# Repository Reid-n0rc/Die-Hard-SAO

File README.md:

# Die Hard SAO
 Come out to the coast, have a few laughs...

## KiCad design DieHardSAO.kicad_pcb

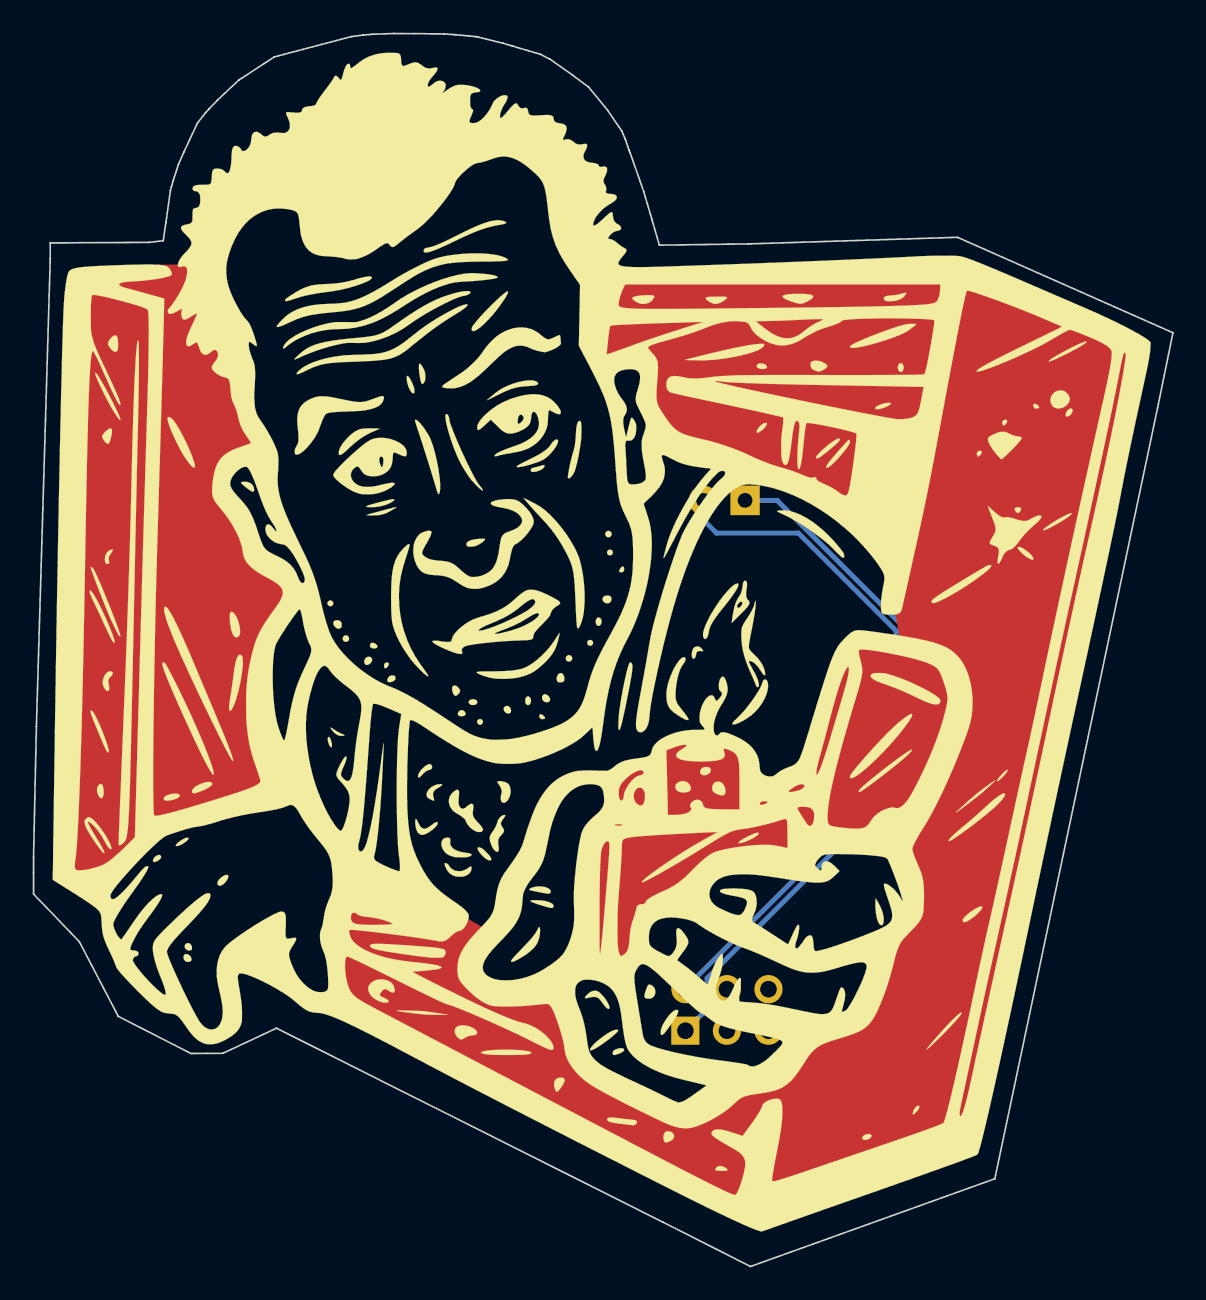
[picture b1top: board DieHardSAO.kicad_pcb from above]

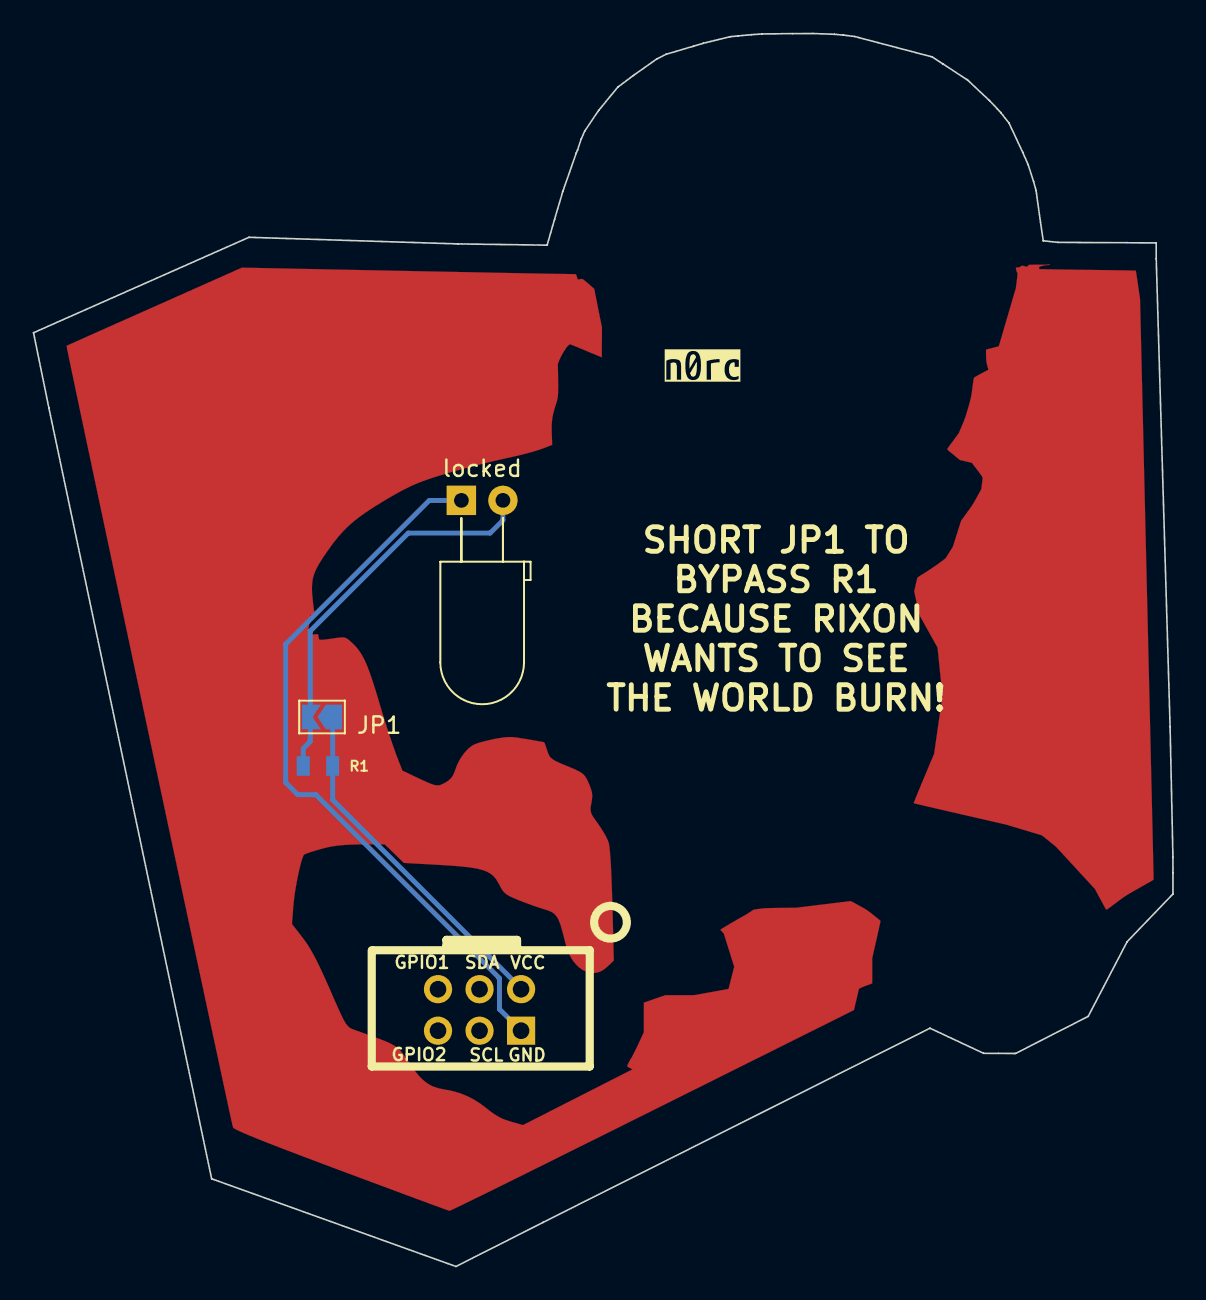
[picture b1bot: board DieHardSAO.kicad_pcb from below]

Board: 2 copper layers, 69.7 x 75.4 mm, 5 parts (4 on the bottom side), 3 nets.

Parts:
JP1: JUMPER-SMT_2_NO; SolderJumper-2_P1.3mm_Open_TrianglePad1.0x1.5mm
R1: 56OHM-0805-1_4W-1%; 0805
X1: locked; Badgelife-SAOv169-BADGE-2x3_Back
kibuzzard-61DF9C8F: G***; kibuzzard-61DF9C8F
locked: LED5MM; LED_D5.0mm_Horizontal_O3.81mm_Z9.0mm

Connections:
unnamed: X1.2 (GND), locked.1 (C)
unnamed: JP1.2, R1.2, locked.2 (A)
unnamed: JP1.1, R1.1, X1.1 (VCC)

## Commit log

2022-09-30 Initial Commit
    Initial commit of the Die Hard SAO
2022-09-30 Cleanup old versions
    Removed old version folders because I was too dumb to start with GitHub
2022-10-05 Changed jumper
    Changed jumper and moved traces
2022-10-05 Changed jumper footprint and clean up
    Changed the jumper footprint.
    Cleaned up auto generated files and added them to the ignore list.
    Change the gerber file output directory from Output/v2 to Output
